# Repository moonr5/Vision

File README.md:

# SGU Logistics & Telemetry Dashboard

> **Intelligent Fleet Management System** — Real-time vehicle telemetry, AI-powered analytics, and logistics optimization across a distributed four-layer architecture spanning embedded hardware, cloud microservices, and a browser-based command center.

---

## Table of Contents

- [System Architecture](#system-architecture)
- [Data Flow](#data-flow)
- [Service Topology](#service-topology)
- [Key Innovations](#key-innovations)
- [Technology Stack](#technology-stack)
- [The 28 AI Engines](#the-28-ai-engines)
- [Project Structure](#project-structure)
- [Database Design](#database-design)
- [Getting Started](#getting-started)
- [API Reference](#api-reference)
- [Testing](#testing)
- [Deployment](#deployment)
- [Documentation Index](#documentation-index)
- [Academic Context](#academic-context)

---

## System Architecture

The platform is organized into four independent layers, each capable of operating with graceful degradation when downstream services are unavailable.

```mermaid
flowchart TB
    subgraph EDGE["HARDWARE / EDGE LAYER"]
        direction LR
        GPS["GPS Module<br/>ESP32"]
        OBD["OBD-II Scanner<br/>ESP32 + MCP2515 CAN"]
        BEH["BehaviorAnalysis<br/>C++ On-Device<br/>7 Safety Checks"]
    end

    subgraph CORE["BACKEND CORE LAYER"]
        direction TB
        SRV["Express Server<br/>server.js :3000"]
        MQTT["MQTT Subscriber<br/>monztrack/device01/#"]
        REST["REST API<br/>30+ Endpoints"]
        SSE["SSE Stream<br/>GET /api/stream"]
        PG[("PostgreSQL 15<br/>Persistent Storage")]
        CONN["Integration Connector<br/>connector.js"]
    end

    subgraph AI["AI / INTELLIGENCE LAYER"]
        direction LR
        subgraph SC["Scale Engine :8002"]
            DI["Data Ingestion ×9"]
            SS["Smart Systems ×8"]
            ML["AI / ML ×8"]
            EC["Edge / Cloud ×3"]
        end
        subgraph RT["Route Engine :8001"]
            RA["Route Analyzer"]
            DM["Driver Matching"]
            RP["Report Pipeline"]
        end
        subgraph AB["AI Backend :8000"]
            GM["Gemini 2.0 Flash"]
            TG["Telegram Bot"]
            PDF["PDF Reports"]
        end
    end

    subgraph PRES["PRESENTATION LAYER"]
        direction TB
        DASH["Web Dashboard<br/>Leaflet + Chart.js"]
        SQLITE[("Browser SQLite<br/>sql.js WASM")]
        AICHAT["AI Chat Interface"]
        AUTH["Authentication"]
    end

    GPS -->|"MQTT"| MQTT
    OBD -->|"MQTT"| MQTT
    BEH -->|"Serial"| OBD

    MQTT --> SRV
    SRV --> PG
    SRV --> SSE
    SRV --> REST
    SRV --> CONN

    CONN -->|"HTTP"| SC
    CONN -->|"HTTP"| RT
    CONN -->|"HTTP"| AB

    SSE --> DASH
    REST --> DASH
    DASH --> SQLITE
    DASH --> AICHAT
    DASH --> AUTH

    GM --> TG
    GM --> PDF
```

---

## Data Flow

End-to-end telemetry journey — sub-200ms from sensor silicon to dashboard pixel.

```mermaid
sequenceDiagram
    autonumber

    participant V as Vehicle Sensors<br/>(OBD-II, GPS, CAN)
    participant ESP as ESP32 Microcontroller
    participant MQTT as MQTT Broker<br/>(HiveMQ)
    participant SRV as Node.js Server<br/>(server.js)
    participant PG as PostgreSQL
    participant SC as Scale Engine<br/>(28 Engines)
    participant SSE as SSE Stream
    participant UI as Dashboard<br/>(Browser)

    loop Every 500ms
        V->>ESP: Read RPM, throttle, coolant, speed, GPS
        ESP->>ESP: BehaviorAnalysis.check()<br/>7 safety thresholds
        ESP->>MQTT: Publish JSON payload<br/>topic: monztrack/device01/gps
    end

    MQTT->>SRV: Subscriber receives (~50ms)
    SRV->>PG: INSERT telemetry (~20ms)
    SRV->>SC: Forward via HTTP (fire-and-forget)

    activate SC
    SC->>SC: Stream Bus routing
    SC->>SC: Normalize & validate schema
    SC->>SC: CEP rule evaluation
    SC->>SC: Anomaly detection
    SC->>SC: Digital Twin update
    SC->>SC: Behavior inference
    deactivate SC

    SRV->>SSE: Push to connected clients (~10ms)
    SSE->>UI: Render update (~16ms)

    Note over V,UI: Total latency: ~200ms sensor-to-screen

    alt Alert triggered
        SC->>SRV: POST /api/events
        SRV->>UI: SSE event notification
        SC->>SC: Telegram Bot send alert
    end
```

### Processing Pipeline Detail

```mermaid
flowchart LR
    subgraph Ingestion["INGESTION (Node.js)"]
        A["MQTT<br/>Subscribe"] --> B["Validate<br/>JSON"]
        B --> C["Persist<br/>PostgreSQL"]
        C --> D["Forward<br/>Scale Engine"]
        C --> E["Broadcast<br/>SSE Stream"]
    end

    subgraph Processing["PROCESSING (Python)"]
        D --> F["Stream Bus<br/>Route to engines"]
        F --> G["Normalize<br/>Units & schema"]
        G --> H["CEP Engine<br/>Rule evaluation"]
        H --> I["Anomaly<br/>Detection"]
        I --> J["Digital Twin<br/>State update"]
        J --> K["Behavior<br/>Inference"]
    end

    subgraph Output["OUTPUT"]
        K --> L["Event<br/>Generation"]
        L --> M["Telegram<br/>Alert"]
        L --> N["Dashboard<br/>Notification"]
        K --> O["Driver Score<br/>Update"]
        K --> P["Predictive<br/>Maintenance Flag"]
    end
```

---

## Service Topology

Four independent microservices connected via HTTP with graceful degradation at every boundary.

```mermaid
flowchart TB
    subgraph External["External Services"]
        BROKER[("MQTT Broker<br/>broker.hivemq.com:1883")]
        GEMINI[("Google Gemini API<br/>gemini-2.0-flash")]
        TELEGRAM[("Telegram Bot API")]
    end

    subgraph Railway["Railway Deployment"]
        subgraph NODE["Node.js Server — :3000"]
            SRV["Express + MQTT + SSE"]
            INT["connector.js<br/>Proxy Layer"]
        end

        subgraph AI_BE["AI Backend — :8000"]
            ANA["FleetAnalyzer"]
            BOT["Telegram Bot"]
            REP["ReportGenerator"]
        end

        subgraph ROUTE["Route Engine — :8001"]
            RANA["RouteAnalyzer"]
            RINT["BehaviorIntegrator"]
            RPIP["ReportPipeline"]
        end

        subgraph SCALE["Scale Engine — :8002"]
            ENGINES["28 Modular Engines<br/>Auto-registered REST endpoints"]
        end

        DB[("PostgreSQL<br/>postgres.railway.internal")]
    end

    BROKER -->|"MQTT :1883"| SRV
    GEMINI -->|"REST"| ANA
    GEMINI -->|"REST"| RANA
    TELEGRAM -->|"Webhook"| BOT

    SRV --> DB
    INT -->|"HTTP *.internal"| AI_BE
    INT -->|"HTTP *.internal"| ROUTE
    INT -->|"HTTP *.internal"| SCALE

    style NODE fill:#e1f5e1,stroke:#2d8a2d
    style AI_BE fill:#e1e5f5,stroke:#2d4a8a
    style ROUTE fill:#f5f0e1,stroke:#8a7a2d
    style SCALE fill:#f5e1e1,stroke:#8a2d2d
```

---

## Key Innovations

### 1. Database-First AI Architecture

The browser-side AI engine queries a local SQLite database before escalating to Gemini. This eliminates API costs for routine analytical questions.

```mermaid
flowchart LR
    Q["User Question"] --> SQL["SQLite Query<br/>(sql.js WASM)"]
    SQL -->|"80-85% answered"| A1["Return Result<br/>Cost: $0"]
    SQL -->|"15-20% complex"| GM["Gemini 2.0 Flash<br/>Context-enhanced prompt"]
    GM --> A2["Return Insight<br/>Cost: ~$0.0001"]

    style SQL fill:#d4edda,stroke:#28a745
    style GM fill:#fff3cd,stroke:#ffc107
```

| Metric | All-Cloud Approach | Database-First Approach |
|--------|-------------------|------------------------|
| Monthly AI API cost | ~$50 | ~$10 |
| Average query latency | 800ms | 50ms (cached) |
| Offline capability | None | Full (SQLite + IndexedDB) |

### 2. 28 Modular AI Engines

Each engine is an independent Python module that auto-registers REST endpoints via FastAPI. Engines discover related peers through a registry pattern — adding a new engine requires zero changes to existing code. Hot-swap individual engines without restarting the scale platform.

### 3. On-Device Safety Detection

The `BehaviorAnalysis` C++ module runs directly on the ESP32, detecting seven unsafe driving behaviors from raw sensor data before transmission. Safety-critical alerts have zero cloud dependency and survive network outages.

| Behavior | Detection Rule | Severity |
|----------|---------------|----------|
| Harsh Braking | Speed drop > 15 km/h within 3 seconds | Warning |
| Aggressive Launch | Throttle > 90% at speed < 30 km/h | Warning |
| Cold Engine Abuse | RPM > 3000 with coolant < 70&deg;C | Warning |
| Engine Lugging | Load > 85% with RPM < 1500 | Warning |
| Excessive Idling | Speed = 0, RPM > 500 for > 180s | Info |
| Speeding | Speed > 110 km/h | Critical |
| Unknown | Custom rule violations | Variable |

### 4. Graceful Degradation at Every Boundary

Every downstream dependency is optional. The integration connector returns structured 503 responses when engines are unreachable. The dashboard continues displaying live telemetry even when the Scale Engine, Route Engine, and AI Backend are all simultaneously offline.

### 5. Predictive Maintenance from OBD Trend Analysis

The Predictive Maintenance engine monitors longitudinal trends in coolant temperature, battery voltage, and RPM stability. Statistical drift detection triggers maintenance flags before components fail, preventing roadside breakdowns.

---

## Technology Stack

| Layer | Technology | Purpose |
|-------|-----------|---------|
| **Embedded** | Arduino C++ (ESP32, MCP2515 CAN controller) | OBD-II data capture, GPS tracking, on-device safety analysis |
| **Messaging** | MQTT 5.0 (HiveMQ public broker) | Real-time publish/subscribe telemetry transport |
| **Application Server** | Node.js 18+ / Express 4.x | REST API, SSE streaming, static asset serving |
| **Server Database** | PostgreSQL 15 | Long-term telemetry persistence, order management, geofencing |
| **Browser Database** | SQLite via sql.js (WebAssembly) | Offline cache, local analytics, cost-free AI query layer |
| **Analytics** | Python 3.9+ / FastAPI | 28 modular AI/ML microservices with auto-generated endpoints |
| **LLM Integration** | Google Gemini 2.0 Flash | Natural language fleet analysis, route scoring, report synthesis |
| **Notifications** | Telegram Bot API (python-telegram-bot) | Real-time alert delivery, on-demand PDF report generation |
| **Frontend** | Leaflet.js, Chart.js, jsPDF, Turf.js | Interactive geospatial visualization, telemetry charts, PDF export |
| **Stream Processing** | Redis Streams / NATS / In-Memory | High-throughput telemetry ingestion and routing |
| **PDF Generation** | Jinja2 + WeasyPrint | Templated PDF fleet reports |
| **Testing** | Jest, fake-indexeddb, jsdom | Isolated unit and integration tests |
| **Deployment** | Railway (Nixpacks) | Containerized, zero-configuration deployment |
| **Code Quality** | ESLint, Prettier | Consistent formatting and static analysis |

---

## The 28 AI Engines

All engines reside in `scale_engine/` and expose REST endpoints automatically through the FastAPI engine registry. Each engine is an independent module — add or remove engines without modifying the platform core.

### Engine Category Overview

```mermaid
flowchart LR
    subgraph DI["Data Ingestion (9)"]
        direction TB
        DI1["Stream Bus"]
        DI2["Timeseries Engine"]
        DI3["Storage Tiers"]
        DI4["Schema Registry"]
        DI5["Normalizer"]
        DI6["Geo Processor"]
        DI7["Fleet State"]
        DI8["Data Quality"]
        DI9["Replay / Backfill"]
    end

    subgraph SS["Smart Systems (8)"]
        direction TB
        SS1["CEP Engine"]
        SS2["Anomaly Detector"]
        SS3["Digital Twin"]
        SS4["Behavior Inference"]
        SS5["Predictive Maintenance"]
        SS6["Fleet Optimizer"]
        SS7["Route ETA"]
        SS8["Signal Fusion"]
    end

    subgraph ML["AI / ML (8)"]
        direction TB
        ML1["Feature Store"]
        ML2["Model Trainer"]
        ML3["Model Server"]
        ML4["Vector RAG"]
        ML5["Forecaster"]
        ML6["Knowledge Graph"]
        ML7["MLOps"]
        ML8["AI Orchestrator"]
    end

    subgraph EC["Edge / Cloud (3)"]
        direction TB
        EC1["Edge Model Manager"]
        EC2["Sync Engine"]
        EC3["Federated Learning"]
    end

    DI --> SS --> ML --> EC
```

### Data Ingestion (Engines 1–9)

| # | Engine | Source File | Responsibility |
|---|--------|------------|----------------|
| 1 | Stream Bus | `data_ingestion/stream_bus.py` | Distributed message routing — Redis Streams, NATS, or in-memory. Handles thousands of data points per second. |
| 2 | Timeseries Engine | `data_ingestion/timeseries_engine.py` | Temporal aggregation with configurable windows (hourly, daily, weekly) on any telemetry metric. |
| 3 | Storage Tiers | `data_ingestion/storage_tiers.py` | Hot/warm/cold data lifecycle management — recent data in memory, aged data in cold storage. |
| 4 | Schema Registry | `data_ingestion/schema_registry.py` | Validates every incoming payload against expected JSON schema; rejects malformed data. |
| 5 | Normalizer | `data_ingestion/normalizer.py` | Unit standardization pipeline — km/h &harr; mph, &deg;C &harr; &deg;F, L &harr; gal. |
| 6 | Geo Processor | `data_ingestion/geo_processor.py` | Geofence evaluation, proximity detection, route corridor analysis. |
| 7 | Fleet State | `data_ingestion/fleet_state.py` | Materialized fleet-wide projection — online count, moving count, idle count, alerting count. |
| 8 | Data Quality | `data_ingestion/data_quality.py` | Sensor health monitoring — stale data detection, gap analysis, outlier flagging. |
| 9 | Replay / Backfill | `data_ingestion/replay_backfill.py` | Historical data replay engine for backfilling telemetry after service downtime. |

### Smart Systems (Engines 10–17)

| # | Engine | Source File | Responsibility |
|---|--------|------------|----------------|
| 10 | CEP Engine | `smart_systems/cep_engine.py` | Complex Event Processing — multi-condition rule chains (e.g., "speeding AND coolant > 110&deg;C" triggers CRITICAL). |
| 11 | Anomaly Detector | `smart_systems/anomaly_detector.py` | Statistical outlier detection across fleet-wide behavior patterns using Z-score and IQR methods. |
| 12 | Digital Twin | `smart_systems/digital_twin.py` | Virtual vehicle state model updated in real-time from the sensor stream — mirrors physical vehicle. |
| 13 | Behavior Inference | `smart_systems/behavior_inference.py` | Longitudinal driver scoring with trend analysis and automated coaching recommendations. |
| 14 | Predictive Maintenance | `smart_systems/predictive_maintenance.py` | Failure probability estimation from OBD trends — coolant, voltage, RPM stability. |
| 15 | Fleet Optimizer | `smart_systems/fleet_optimizer.py` | Dispatch optimization — driver-to-order matching, load balancing, schedule optimization. |
| 16 | Route ETA | `smart_systems/route_eta.py` | ETA prediction engine with and without driver behavior history features. |
| 17 | Signal Fusion | `smart_systems/signal_fusion.py` | Multi-sensor fusion (GPS + OBD + accelerometer) for higher-accuracy speed and position estimation. |

### AI / ML (Engines 18–25)

| # | Engine | Source File | Responsibility |
|---|--------|------------|----------------|
| 18 | Feature Store | `ai_ml/feature_store.py` | Computes feature vectors from raw telemetry for ML model training and inference. |
| 19 | Model Trainer | `ai_ml/model_trainer.py` | Trains ML models — driver risk classification, fuel efficiency regression, maintenance prediction. |
| 20 | Model Server | `ai_ml/model_server.py` | Low-latency model inference serving for real-time prediction requests. |
| 21 | Vector RAG | `ai_ml/vector_rag.py` | Retrieval-Augmented Generation with semantic vector search over fleet operational history. |
| 22 | Forecaster | `ai_ml/forecaster.py` | Time-series forecasting for fuel consumption and delivery delay prediction. |
| 23 | Knowledge Graph | `ai_ml/knowledge_graph.py` | Fleet-wide relationship model — drivers, vehicles, routes, orders, and their interactions. |
| 24 | MLOps | `ai_ml/mlops.py` | Model lifecycle management — versioning, drift detection, automated rollback triggers. |
| 25 | AI Orchestrator | `ai_ml/ai_orchestrator.py` | Multi-agent coordination layer — routes tasks between engines based on capability registry. |

### Edge / Cloud Bridge (Engines 26–28)

| # | Engine | Source File | Responsibility |
|---|--------|------------|----------------|
| 26 | Edge Model Manager | `edge_cloud/edge_model_mgr.py` | Model compression, quantization, and rollout to edge devices with confirmation tracking. |
| 27 | Sync Engine | `edge_cloud/sync_engine.py` | Bidirectional cloud-to-edge data synchronization with conflict resolution. |
| 28 | Federated Learning | `edge_cloud/federated_learning.py` | Federated learning round management — models improve from edge data without raw data leaving the device. |

### System Introspector

| Engine | Source File | Responsibility |
|--------|------------|----------------|
| System Analyzer | `system_analyzer.py` | AI-powered full-system introspection — engine health, data flow status, cross-service diagnostics. |

---

## Project Structure

```
Vision/
|
|-- Frontend
|   |-- index.html                   Main dashboard (Leaflet maps, Chart.js, AI chat)
|   |-- login.html                   Authentication page
|   |-- login.js                     Authentication logic
|   |-- login.css                    Authentication styles
|   +-- z_logo.png                   Project brand asset
|
|-- Backend (Node.js)
|   |-- server.js                    Express server — MQTT, REST API, SSE, proxy
|   |-- package.json                 Dependencies and npm scripts
|   |-- .env.example                 Environment variable template with documentation
|   |-- .eslintrc.cjs                ESLint configuration
|   |-- .prettierrc                  Prettier configuration
|   +-- jest.config.js               Jest test runner configuration
|
|-- Integration Bridge
|   +-- integration/
|       +-- connector.js             HTTP proxy layer — Node.js to Python microservices
|
|-- AI Engines (Python / FastAPI)
|   |-- scale_engine/                Port 8002 — 28-engine intelligence platform
|   |   |-- main.py                  FastAPI application & engine registry
|   |   |-- system_analyzer.py       AI system introspection engine
|   |   |-- db.py                    Engine database utilities
|   |   |-- data_ingestion/          9 engines — stream bus, timeseries, geo, etc.
|   |   |-- smart_systems/           8 engines — CEP, anomaly, digital twin, etc.
|   |   |-- ai_ml/                   8 engines — feature store, models, forecast, etc.
|   |   +-- edge_cloud/              3 engines — edge models, sync, federated learning
|   |
|   |-- route_engine/                Port 8001 — Route optimization service
|   |   |-- main.py                  FastAPI application
|   |   |-- route_analyzer.py        Hybrid AI + deterministic route scoring
|   |   |-- behavior_integrator.py   Driver behavior data integration
|   |   |-- report_pipeline.py       4-stage report generation pipeline
|   |   +-- db.py                    Route database queries
|   |
|   +-- ai_backend/                  Port 8000 — AI analysis & Telegram notifications
|       |-- main.py                  FastAPI application
|       |-- analyzer.py              Fleet analyzer (Gemini 2.0 Flash wrapper)
|       |-- telegram_bot.py          Telegram bot command handlers
|       |-- report_generator.py      PDF report generator (Jinja2 + WeasyPrint)
|       +-- db.py                    Fleet snapshot query helpers
|
|-- Database Module
|   +-- database/
|       |-- db.js                    Core SQLite engine (sql.js WASM) — init, auto-save
|       |-- dal.js                   Data Access Layer — typed CRUD for all 12 tables
|       |-- service.js               High-level service API with business logic
|       |-- ai-engine.js             Smart AI — SQLite-first query, Gemini fallback
|       |-- migrate.js               Legacy localStorage to SQLite migration
|       |-- integration.js           Global function patching for database use
|       |-- loader.js                Single script include for HTML pages
|       |-- schema.sql               Browser SQLite schema (12 tables)
|       |-- pg-schema.sql            PostgreSQL schema (12 tables + 4 views)
|       +-- README.md                Database architecture reference
|
|-- Embedded Firmware (Arduino C++)
|   |-- GPS_device.ino               GPS module firmware (ESP32)
|   |-- obd2_scanner.ino             OBD-II CAN bus scanner (ESP32 + MCP2515)
|   |-- BehaviorAnalysis.h           On-device safety detection (header)
|   +-- BehaviorAnalysis.cpp         On-device safety detection (implementation)
|
|-- Test Suite
|   +-- tests/
|       |-- server.test.js           7 server integration tests
|       |-- helpers/
|       |   |-- server-process.js    Isolated server process manager
|       |   +-- browser-db-harness.js Browser DB test environment (jsdom)
|       +-- database/
|           |-- ai-engine.test.js    Smart AI engine unit tests
|           |-- dal.test.js          Data Access Layer unit tests
|           +-- db.test.js           Core database unit tests
|
|-- Documentation
|   |-- README.md                    Primary project documentation
|   |-- FULL_SYSTEM_DECOMPOSITION.md Complete 6-layer architectural decomposition
|   |-- SYSTEM_AT_A_GLANCE.md        Visual reference with system diagrams
|   |-- THESIS_EXPLANATION.md        Thesis overview, innovations, and Q&A
|   |-- PRESENTATION_GUIDE.md        Defense presentation guide and talking points
|   |-- Code Architecture.drawio     Full visual architecture diagram (Draw.io)
|   +-- root/About/
|       |-- AI-UPGRADE.md            AI architecture evolution narrative
|       +-- AI-TEST.md               Database-first AI testing methodology
|
+-- Deployment
    |-- railway.json                 Node.js server deployment configuration
    |-- ai_backend/railway.json      AI backend deployment configuration
    |-- route_engine/railway.json    Route engine deployment configuration
    +-- scale_engine/railway.json    Scale engine deployment configuration
```

---

## Database Design

Dual-database architecture — PostgreSQL for server-side persistence, SQLite (WebAssembly) for browser-side caching. Both databases share schema parity across 12 tables.

```mermaid
erDiagram
    drivers ||--o{ devices : "assigned to"
    drivers ||--o{ orders : "delivers"
    drivers ||--o{ trips : "performs"
    drivers ||--o{ driver_behavior_history : "generates"
    devices ||--o{ telemetry : "produces"
    devices ||--o{ geofence_events : "triggers"
    orders ||--o{ trips : "tracked by"
    orders }o--|| customers : "placed by"
    geofences ||--o{ geofence_events : "defines"
    telemetry ||--o{ events : "may trigger"

    drivers {
        int id PK
        string name
        string license_number
        float safety_score
        json behavior_events
        int vehicle_id FK
    }

    devices {
        int id PK
        string device_identifier
        string mqtt_topic
        boolean is_online
        int driver_id FK
    }

    telemetry {
        bigint id PK
        int device_id FK
        json gps
        json obd2
        json fuel
        json sensor
        json raw_payload
        timestamp recorded_at
    }

    orders {
        int id PK
        int driver_id FK
        int device_id FK
        int customer_id FK
        json origin
        json destination
        string cargo_type
        string status
    }

    events {
        int id PK
        int device_id FK
        string type
        string category
        string severity
        json sensor_state
        boolean acknowledged
    }

    trips {
        int id PK
        int driver_id FK
        int order_id FK
        float duration
        float distance
        float avg_speed
        float fuel_used
        int event_count
    }
```

### Database Views

| View | Purpose |
|------|---------|
| `v_active_orders` | Orders not yet completed or cancelled, joined with driver and device info |
| `v_device_latest_telemetry` | Most recent telemetry record per device (avoids expensive subquery) |
| `v_event_summary_24h` | Event counts grouped by type within the trailing 24-hour window |
| `v_order_stats` | Order aggregations — counts by status, type, and assigned driver |

Full schema definitions: [database/pg-schema.sql](database/pg-schema.sql) (PostgreSQL, 293 lines) | [database/schema.sql](database/schema.sql) (SQLite, 456 lines)

---

## Getting Started

### Prerequisites

| Software | Minimum Version | Required | Purpose |
|----------|----------------|----------|---------|
| Node.js | 18.0.0 | Required | Express application server |
| Python | 3.9 | Optional | AI microservices (degrade gracefully if absent) |
| PostgreSQL | 15 | Optional | Persistent telemetry storage |
| Arduino IDE | 2.x | Optional | ESP32 firmware deployment |
| Gemini API Key | — | Optional | AI-powered analysis features |

### 1. Clone and Install

```bash
git clone https://github.com/moonr5/Vision.git
cd Vision
npm install
```

### 2. Configure Environment

```bash
cp .env.example .env
```

| Variable | Required | Default | Description |
|----------|----------|---------|-------------|
| `DATABASE_URL` | For persistence | — | PostgreSQL connection string |
| `PORT` | No | `3000` | Express server port |
| `GEMINI_API_KEY` | No | — | Google Gemini API key |
| `TELEGRAM_BOT_TOKEN` | No | — | Telegram bot token from @BotFather |
| `TELEGRAM_CHAT_ID` | No | — | Restrict bot to a single chat ID |
| `PYTHON_AI_URL` | No | — | AI backend service URL |
| `ROUTE_ENGINE_URL` | No | — | Route engine service URL |
| `SCALE_ENGINE_URL` | No | — | Scale engine service URL |

### 3. Start the Server

```bash
npm start
```

The dashboard is available at `http://localhost:3000`.

### 4. Start Python Microservices (Optional)

Each service runs independently and the system degrades gracefully without them.

```bash
# Terminal 1 — AI Backend (Gemini analysis + Telegram bot)
cd ai_backend
pip install -r requirements.txt
uvicorn main:app --port 8000

# Terminal 2 — Route Engine (route optimization)
cd route_engine
pip install -r requirements.txt
uvicorn main:app --port 8001

# Terminal 3 — Scale Engine (28 AI engines)
cd scale_engine
pip install -r requirements.txt
uvicorn main:app --port 8002
```

### 5. Deploy Arduino Firmware

1. Open `obd2_scanner.ino` in the Arduino IDE
2. Select board: **ESP32 Dev Module**
3. Configure WiFi SSID and password in the sketch
4. Wire the MCP2515 CAN controller to the ESP32 SPI pins
5. Upload to the device

---

## API Reference

### Node.js Application Server — Port 3000

| Method | Endpoint | Response | Description |
|--------|----------|----------|-------------|
| `GET` | `/` | `text/html` | Authentication page |
| `GET` | `/api/stream` | `text/event-stream` | Server-Sent Events live telemetry feed |
| `GET` | `/api/telemetry/latest` | `application/json` | Most recent telemetry record per device |
| `GET` | `/api/telemetry/:deviceId` | `application/json` | Telemetry history for a device (limit: 1000) |
| `GET` | `/api/events` | `application/json` | Recent events across all devices (limit: 500) |
| `GET` | `/api/devices` | `application/json` | All registered IoT devices with status |
| `POST` | `/api/ai/analyze` | `application/json` | Proxy analysis request to Python AI backend |
| `GET` | `/health` | `application/json` | Full system health — DB, MQTT, SSE, all engines |

### Route Engine — Port 8001

| Method | Endpoint | Description |
|--------|----------|-------------|
| `POST` | `/api/route/analyze` | Score three candidate routes across five dimensions for a given driver |
| `POST` | `/api/route/compare` | Compare routes without driver context; optionally rank drivers for the best route |
| `POST` | `/api/route/driver-match` | Find the optimal driver for a fixed route based on behavior history |
| `POST` | `/api/route/report` | Execute the four-stage report pipeline (Collect, Analyze, AI-Synthesize, Output) |
| `GET` | `/api/route/driver/{id}` | Retrieve a driver's complete behavior profile |
| `GET` | `/api/route/drivers` | List all drivers with behavior summaries |

### Scale Engine — Port 8002

Fifty-plus auto-registered endpoints — one per engine. See [scale_engine/main.py](scale_engine/main.py) for the complete engine registry and endpoint map.

### AI Backend — Port 8000

| Method | Endpoint | Description |
|--------|----------|-------------|
| `POST` | `/api/ai/analyze` | Fleet-wide analysis via Gemini 2.0 Flash with database context |
| `POST` | `/api/ai/telegram-webhook` | Telegram Bot API webhook endpoint |

---

## Testing

```bash
npm test                  # Full test suite (sequential execution)
npm run test:server       # Server integration tests only
npm run test:database     # Database module tests only
npm run lint              # ESLint static analysis
npm run lint:fix          # ESLint with automatic fixes
npm run format            # Prettier formatting
npm run format:check      # Prettier format verification
```

### Test Architecture

```mermaid
flowchart LR
    subgraph Server["Server Tests"]
        S1["Health endpoint"]
        S2["Empty arrays (no DB)"]
        S3["AI proxy 503"]
        S4["Login page serve"]
        S5["Schema file exists"]
    end

    subgraph DB["Database Tests"]
        D1["Core: init, CRUD, persistence"]
        D2["DAL: typed operations"]
        D3["AI Engine: SQLite-first logic"]
    end

    subgraph Infrastructure["Test Infrastructure"]
        J["Jest Runner"]
        FDB["fake-indexeddb"]
        JSDOM["jsdom"]
        SPM["Server Process Manager"]
    end

    Server --> J
    DB --> J
    J --> FDB
    J --> JSDOM
    J --> SPM
```

| Test File | Coverage | Dependencies |
|-----------|----------|--------------|
| [tests/server.test.js](tests/server.test.js) | 7 integration tests — health checks, proxy behavior, static serving | Jest |
| [tests/database/db.test.js](tests/database/db.test.js) | Core SQLite — initialization, CRUD operations, IndexedDB persistence | Jest + fake-indexeddb |
| [tests/database/dal.test.js](tests/database/dal.test.js) | Data Access Layer — typed operations for all tables | Jest + jsdom |
| [tests/database/ai-engine.test.js](tests/database/ai-engine.test.js) | Smart AI — database-first query routing and fallback logic | Jest + jsdom |

---

## Deployment

### Railway (Recommended)

Each service deploys independently via Nixpacks with zero configuration. Services communicate over Railway's private network (`*.railway.internal`).

```mermaid
flowchart TB
    subgraph Railway["Railway Project"]
        subgraph S1["Node.js Server"]
            NS["server.js<br/>Port 3000"]
        end
        subgraph S2["AI Backend"]
            AB["main.py<br/>Port 8000"]
        end
        subgraph S3["Route Engine"]
            RE["main.py<br/>Port 8001"]
        end
        subgraph S4["Scale Engine"]
            SE["main.py<br/>Port 8002"]
        end
        subgraph S5["PostgreSQL"]
            DB[("Port 5432")]
        end
    end

    NS -->|"private network"| AB
    NS -->|"private network"| RE
    NS -->|"private network"| SE
    NS --> DB

    Internet((Internet)) -->|"HTTPS"| NS
    Internet -->|"HTTPS"| AB
```

```bash
# Deploy each service independently
railway up                          # Node.js server
cd ai_backend && railway up         # AI backend
cd route_engine && railway up       # Route engine
cd scale_engine && railway up       # Scale engine
```

Each service directory contains its own `railway.json` (runtime configuration) and `nixpacks.toml` (build configuration).

### Visual Architecture Diagram

The file [Code Architecture.drawio](Code%20Architecture.drawio) contains the complete system integration map. Open with [app.diagrams.net](https://app.diagrams.net/).

---

## Documentation Index

| Document | Content |
|----------|---------|
| [README.md](README.md) | Primary documentation — architecture, data flow, API reference, setup guide |
| [FULL_SYSTEM_DECOMPOSITION.md](FULL_SYSTEM_DECOMPOSITION.md) | Complete architectural decomposition of all six system layers with extension points |
| [SYSTEM_AT_A_GLANCE.md](SYSTEM_AT_A_GLANCE.md) | Visual quick-reference with system diagrams, folder map, and data journey sequence |
| [THESIS_EXPLANATION.md](THESIS_EXPLANATION.md) | Thesis executive summary, five innovation claims, use cases, common Q&A |
| [PRESENTATION_GUIDE.md](PRESENTATION_GUIDE.md) | Defense presentation structure, 30-second elevator pitch, demo script, anticipated questions |
| [database/README.md](database/README.md) | Database architecture, API reference, schema documentation, troubleshooting guide |
| [root/About/AI-UPGRADE.md](root/About/AI-UPGRADE.md) | Evolution from cloud-only AI to database-first architecture |
| [root/About/AI-TEST.md](root/About/AI-TEST.md) | Methodology for testing the SQLite-first AI query engine |
| [Code Architecture.drawio](Code%20Architecture.drawio) | Full visual system architecture diagram |

---

## Academic Context

This project was developed as a university capstone thesis, demonstrating competency across the full engineering stack:

| Domain | Implementation |
|--------|---------------|
| **IoT & Fog Computing** | Edge processing on ESP32 — safety detection runs on-device, independent of cloud connectivity |
| **Distributed Systems** | Four independent microservices with structured graceful degradation at every integration boundary |
| **Machine Learning Pipeline** | Twenty-eight engines spanning the complete ML lifecycle — ingestion, feature engineering, training, serving, monitoring, and edge deployment |
| **Database Architecture** | Dual PostgreSQL + SQLite design with full schema parity and automated migration between tiers |
| **Full-Stack Engineering** | Hardware (C++) to application server (Node.js) to AI services (Python) to presentation layer (HTML5/JavaScript) |
| **Cost-Efficient AI Design** | Empirical demonstration that a database-first query architecture eliminates 80–85% of LLM API calls without reducing analytical capability |

---

## License

This project is released under the **SGU Logistics Source Available License v1.0**
— a custom license written specifically for this system.

| Permission | Status |
|------------|--------|
| Academic use (research, coursework, thesis) | Permitted |
| Personal / hobbyist use | Permitted |
| Modification and redistribution (non-commercial) | Permitted with attribution |
| Commercial use (SaaS, managed services, paid products) | Requires separate agreement |
| Patent grant | Not included (negotiable for commercial) |

See [LICENSE](LICENSE) for the complete terms and [COPYRIGHT](COPYRIGHT) for
third-party attribution.

---

<p align="center">
  <sub>Built for safer, smarter fleet operations — Arduino &bull; Node.js &bull; Python &bull; PostgreSQL &bull; Gemini AI</sub>
</p>

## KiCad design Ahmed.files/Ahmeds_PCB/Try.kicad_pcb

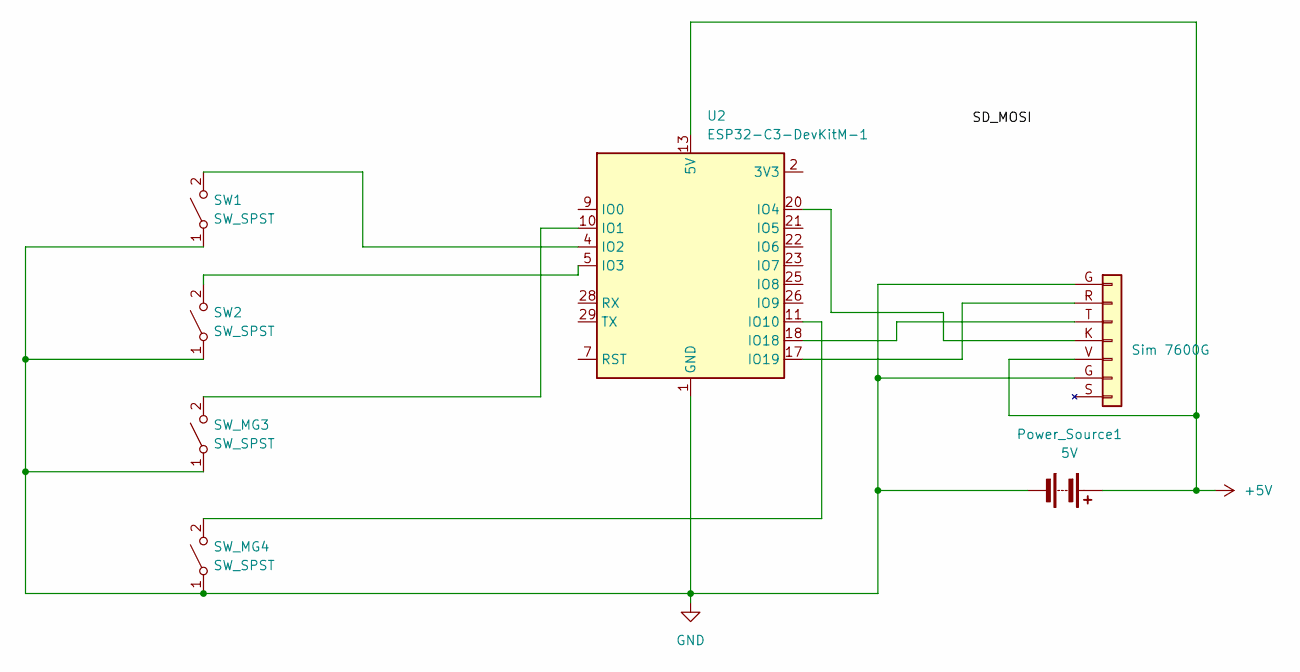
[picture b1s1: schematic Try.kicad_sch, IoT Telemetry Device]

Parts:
J2: Sim 7600G; PinSocket_1x07_P2.54mm_Vertical
Power_Source1: 5V; PinSocket_1x02_P2.54mm_Vertical
SW1, SW2: SW_SPST; PinSocket_1x02_P2.54mm_Vertical
SW_MG3, SW_MG4: SW_SPST; PinSocket_1x02_P2.54mm_Vertical
U2: ESP32-C3-DevKitM-1

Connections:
+5V: J2.V (Pin_5), Power_Source1.1 (+), U2.13 (5V), U2.14 (5V)
GND: J2.G (Pin_1), Power_Source1.2 (-), SW1.1 (A), SW2.1 (A), SW_MG3.1 (A), SW_MG4.1 (A), U2.1 (GND), U2.6 (GND), U2.8 (GND), U2.12 (GND), U2.15 (GND), U2.16 (GND), U2.19 (GND), U2.24 (GND), U2.27 (GND), U2.30 (GND)
unnamed: J2.R (Pin_2), U2.17 (IO19)
unnamed: J2.T (Pin_3), U2.18 (IO18)
unnamed: J2.K (Pin_4), U2.20 (IO4)
unnamed: SW1.2 (B), U2.4 (IO2)
unnamed: SW2.2 (B), U2.5 (IO3)
unnamed: SW_MG3.2 (B), U2.10 (IO1)
unnamed: SW_MG4.2 (B), U2.11 (IO10)
unnamed: U2.2 (3V3), U2.3 (3V3)

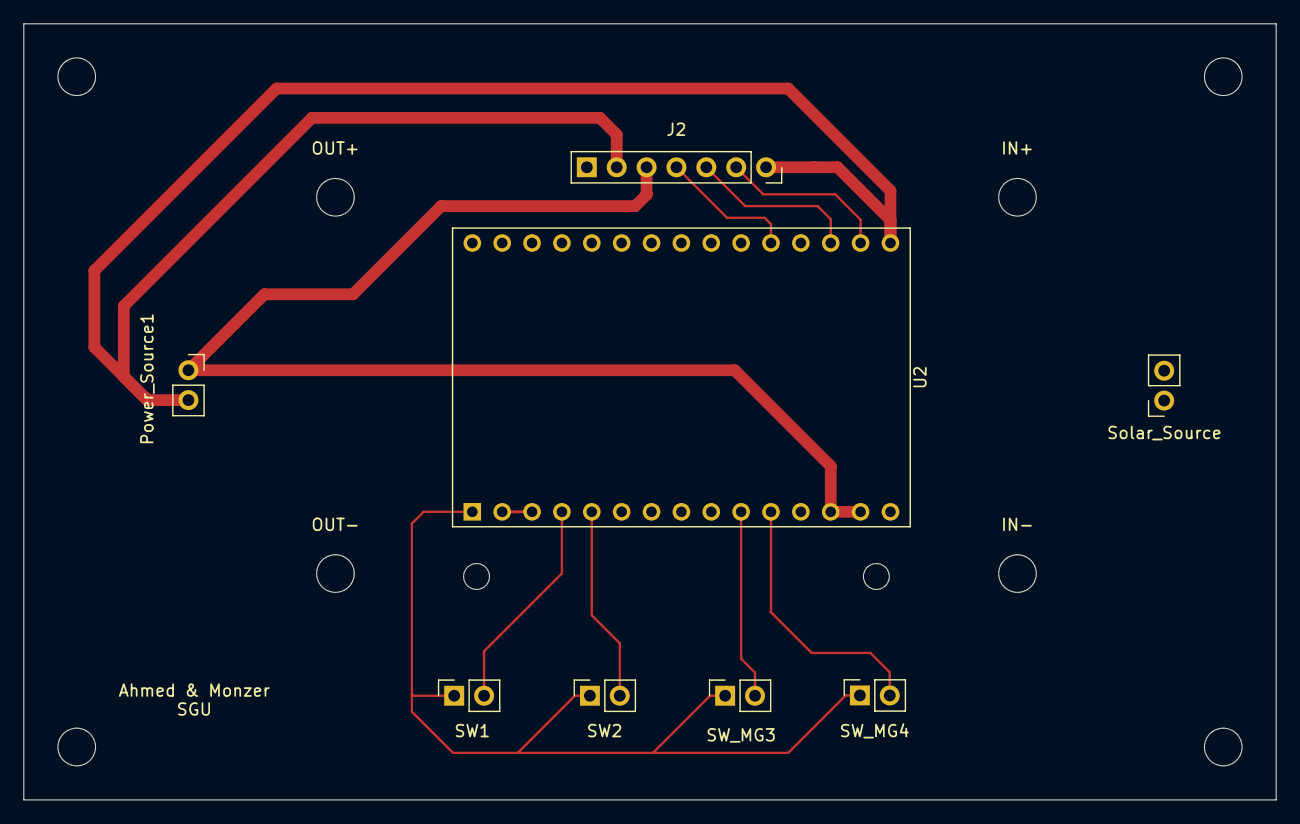
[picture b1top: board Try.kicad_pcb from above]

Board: 2 copper layers, 106.5 x 66.0 mm, 16 parts (0 on the bottom side), 10 nets.

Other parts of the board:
IN+: MountingHole_3.2mm_M3
IN+#2, IN+#3, IN+#4, IN+#5: MountingHole_3.2mm_M3
IN-: MountingHole_3.2mm_M3
OUT+: MountingHole_3.2mm_M3
OUT-: MountingHole_3.2mm_M3
Solar_Source: 5V; PinSocket_1x02_P2.54mm_Vertical

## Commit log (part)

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2026-04-08 add initial project files
2026-05-01 Add Railway deployment, Python AI backend, Telegram PDF reports, and login update
    - Node.js/Express server with PostgreSQL support and static file serving
    - Python AI backend (FastAPI + Gemini) with fleet analysis endpoint
    - Telegram bot that generates PDF fleet reports via WeasyPrint + Jinja2
    - asyncpg database layer for fleet data queries
    - PostgreSQL schema migration on startup
    - Login page updated: any email accepted, password is 'monzer'
2026-05-01 Restore credentials in .env.example (private repo)
2026-05-01 Implement HiveMQ → Railway Backend → PostgreSQL → Dashboard data flow
    - server.js subscribes to HiveMQ via mqtt npm package (server-side TCP)
    - Each MQTT message is persisted to telemetry + devices tables in PostgreSQL
    - New SSE endpoint /api/stream pushes live telemetry to connected dashboards
    - New REST endpoints: /api/telemetry/latest, /api/telemetry/:deviceId, /api/events, /api/devices
    - Dashboard now connects via SSE (/api/stream) with automatic fallback to direct
    Paho MQTT when backend is unavailable (local dev or backend not deployed)
2026-05-01 Add Railway PostgreSQL connection string
2026-05-01 Fix auth check — allow any email, not just hardcoded one
2026-05-01 Add Telegram /report command — generates and sends PDF directly from browser
2026-05-02 Optimize mobile view — map first, horizontal order strip, compact header
2026-06-18 Add comprehensive README and full project documentation
    - Add README.md with architecture diagrams, data flow, 28 AI engines
    breakdown, API reference, tech stack, and getting started guide
    - Add FULL_SYSTEM_DECOMPOSITION.md: deep dive into all 6 system layers
    - Add SYSTEM_AT_A_GLANCE.md: visual reference with ASCII diagrams
    - Add THESIS_EXPLANATION.md: full thesis overview and Q&A
    - Add PRESENTATION_GUIDE.md: supervisor presentation slide guide
2026-06-18 Redesign README with Mermaid diagrams and professional formatting
    - Replace all ASCII art with GitHub-native Mermaid diagrams:
    - System architecture flowchart (4-layer deployment view)
    - End-to-end data flow sequence diagram (sensor to screen)
    - Service topology diagram (Railway deployment)
    - Database-first AI cost comparison flowchart
    - AI engine category relationship diagram
2026-06-18 Add official MIT License file
2026-06-18 Add official LGPLv3 license and repository policies
    - Replace MIT with full LGPLv3 license (includes GPLv3 text)
    - Add COPYRIGHT file with author attribution and third-party notices
    - Add SECURITY.md with vulnerability reporting and deployment guidance
    - Add CONTRIBUTING.md with development workflow and PR process
    - Update README badge and license section to LGPLv3
2026-06-18 Replace LGPLv3 with original custom license written for this system
    Add SGU Logistics Source Available License v1.0 — a custom license
    tailored specifically for this fleet management platform:
    - Permits academic, personal, and non-commercial use with attribution
    - Requires separate agreement for commercial use
    - Includes data privacy and telemetry liability clauses
    - Covers all system components (Node.js, Python engines, Arduino, DB schemas)
2026-06-18 Update report generator and telegram bot captions
2026-06-18 Add project assets

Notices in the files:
README.md:
License: SGU Source Available v1.0
